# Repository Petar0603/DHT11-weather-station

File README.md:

# DHT11-weather-station
Weather station with DHT11 sensor, PCB is made in KiCad 9.0 and STM32 microcontroller code is for Arduino IDE.

---
## About
DHT11 sensor is temperature and humidity sensor, it's output is presented on an SSD1306 OLED display.
Power supply circuit is based on MB102 protoboard power supply, it is used for 3.3V stable output.
STM32F103C8T6 microcontroller is used, programming is done via SWD (Serial Wire Debug).

---
## PCB
For PCB, libraries for DHT11 and 32.768kHz crystal oscillator needed to be made in KiCad.
<div align="center">  </div>

---
## Prototype
<div align="center">  </div>
A more detailed look on connections on the protoboard.
<div align="center">  </div>

---

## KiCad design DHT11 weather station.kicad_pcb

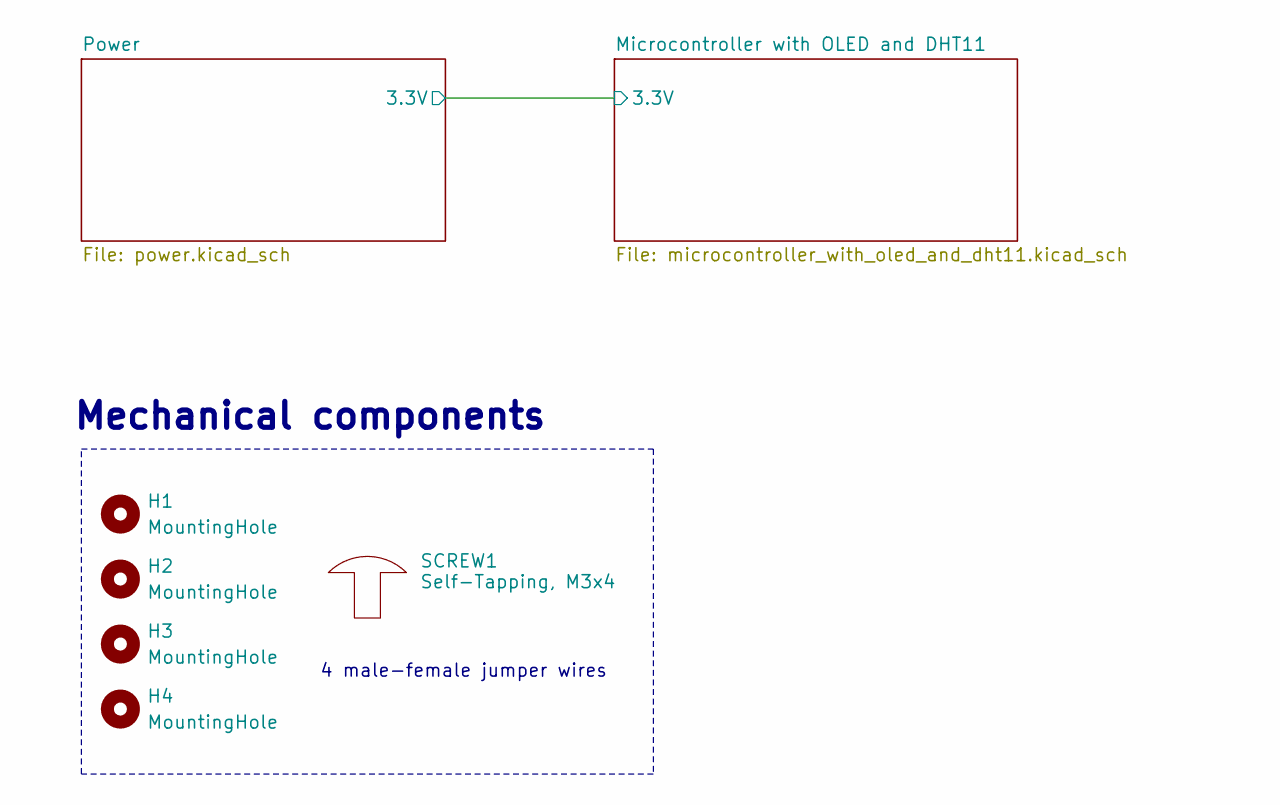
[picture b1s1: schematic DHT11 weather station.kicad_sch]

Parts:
H1, H2, H3, H4: MountingHole; MountingHole_3.2mm_M3
SCREW1: Self-Tapping, M3x4; Farnell 1420120

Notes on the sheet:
Mechanical components
4 male-female jumper wires

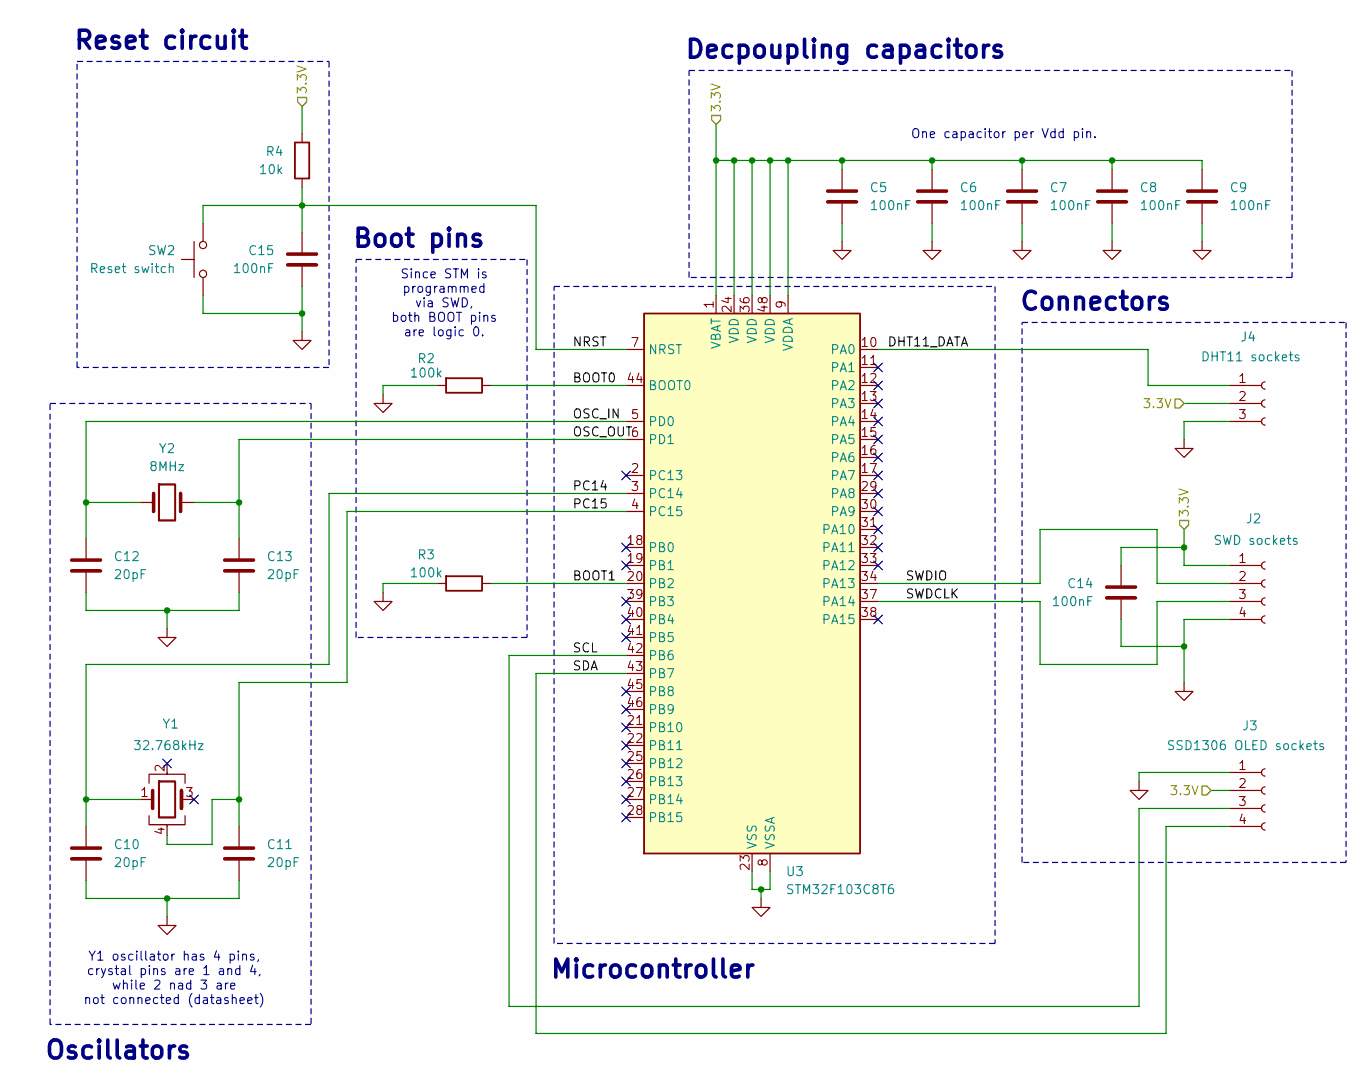
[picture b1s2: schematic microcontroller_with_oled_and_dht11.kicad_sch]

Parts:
C5, C6, C7, C8, C9, C14, C15: 100nF; C_1206_3216Metric
C10, C11, C12, C13: 20pF; C_1206_3216Metric
J2: SWD sockets; PinSocket_1x04_P2.54mm_Horizontal
J3: SSD1306 OLED sockets; PinSocket_1x04_P2.54mm_Horizontal
J4: DHT11 sockets; DHT11
R2, R3: 100k; R_1206_3216Metric
R4: 10k; R_1206_3216Metric
SW2: Reset switch; SW_Tactile_SPST_Angled_PTS645Vx83-2LFS
U3: STM32F103C8T6; LQFP-48_7x7mm_P0.5mm
Y1: 32.768kHz; XTAL_MC-306_32.7680K-G0_ROHS
Y2: 8MHz; Crystal_SMD_HC49-SD

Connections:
/Microcontroller with OLED and DHT11/3.3V: C5.1, C6.1, C7.1, C8.1, C9.1, C14.1, J2.1, J3.2, J4.2, R4.1, U3.1 (VBAT), U3.9 (VDDA), U3.24 (VDD), U3.36 (VDD), U3.48 (VDD); also elsewhere on the board
/Microcontroller with OLED and DHT11/BOOT0: R2.1, U3.44 (BOOT0)
/Microcontroller with OLED and DHT11/BOOT1: R3.1, U3.20 (PB2)
/Microcontroller with OLED and DHT11/DHT11_DATA: J4.1, U3.10 (PA0)
/Microcontroller with OLED and DHT11/NRST: C15.1, R4.2, SW2.1, U3.7 (NRST)
/Microcontroller with OLED and DHT11/OSC_IN: C12.1, U3.5 (PD0), Y2.1
/Microcontroller with OLED and DHT11/OSC_OUT: C13.1, U3.6 (PD1), Y2.2
/Microcontroller with OLED and DHT11/PC14: C10.1, U3.3 (PC14), Y1.1
/Microcontroller with OLED and DHT11/PC15: C11.1, U3.4 (PC15), Y1.4
/Microcontroller with OLED and DHT11/SCL: J3.3, U3.42 (PB6)
/Microcontroller with OLED and DHT11/SDA: J3.4, U3.43 (PB7)
/Microcontroller with OLED and DHT11/SWDCLK: J2.3, U3.37 (PA14)
/Microcontroller with OLED and DHT11/SWDIO: J2.2, U3.34 (PA13)
GND: C5.2, C6.2, C7.2, C8.2, C9.2, C10.2, C11.2, C12.2, C13.2, C14.2, C15.2, J2.4, J3.1, J4.3, R2.2, R3.2, SW2.2, U3.8 (VSSA), U3.23 (VSS), U3.35 (VSS), U3.47 (VSS); also elsewhere on the board

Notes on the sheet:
One capacitor per Vdd pin.
Y1 oscillator has 4 pins, crystal pins are 1 and 4, while 2 nad 3 are not connected (datasheet)
Oscillators
Boot pins
Reset circuit
Microcontroller
Connectors
Decpoupling capacitors
Since STM is programmed via SWD, both BOOT pins are logic 0.

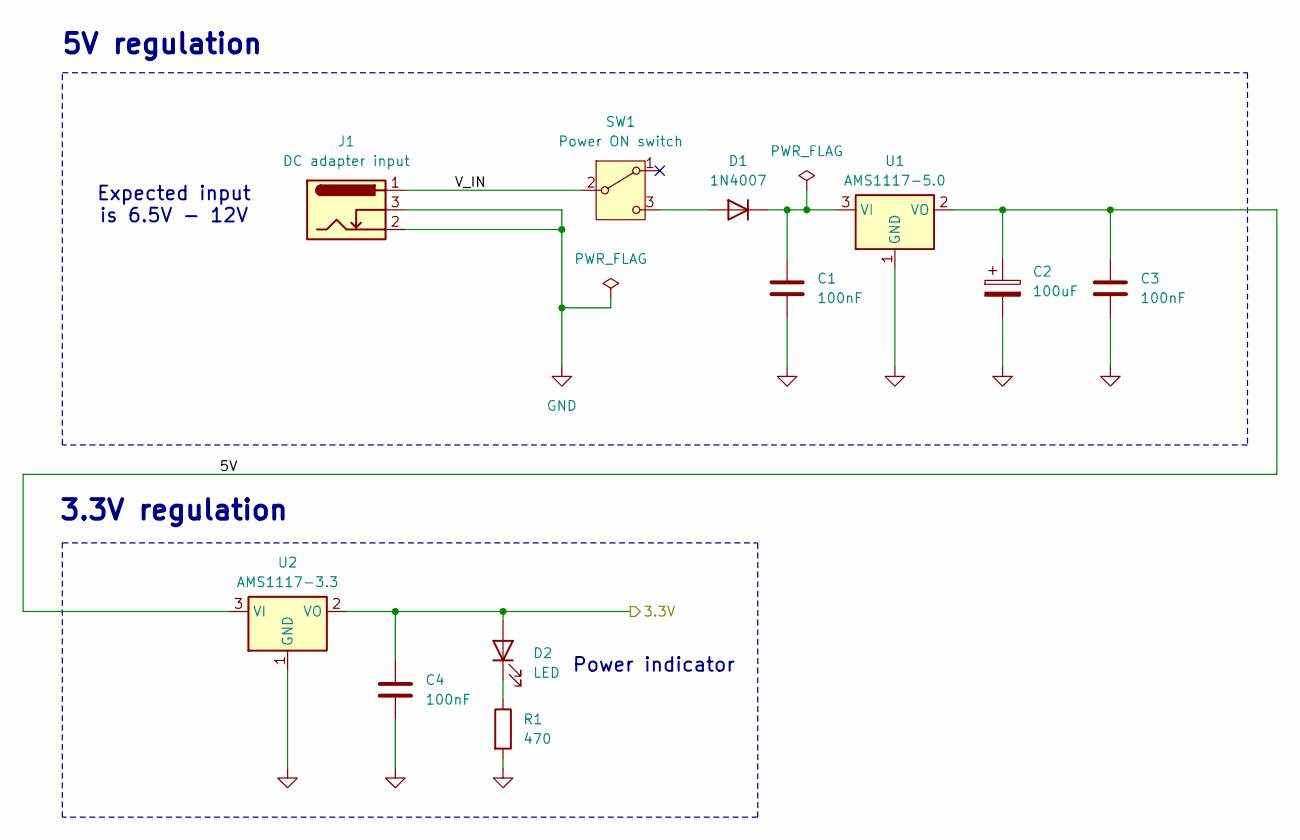
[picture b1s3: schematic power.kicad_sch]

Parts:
C1, C3, C4: 100nF; C_1206_3216Metric
C2: 100uF; CP_Radial_D4.0mm_P2.00mm
D1: 1N4007; D_SMA
D2: LED; LED_D5.0mm_Horizontal_O6.35mm_Z3.0mm
J1: DC adapter input; BarrelJack_GCT_DCJ200-10-A_Horizontal
R1: 470; R_1206_3216Metric
SW1: Power ON switch; SW_E-Switch_EG1224_SPDT_Angled
U1: AMS1117-5.0; SOT-223-3_TabPin2
U2: AMS1117-3.3; SOT-223-3_TabPin2

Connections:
/Microcontroller with OLED and DHT11/3.3V: C4.1, D2.2 (A), U2.2 (VO); also elsewhere on the board
/Power/5V: C2.1, C3.1, U1.2 (VO), U2.3 (VI)
/Power/V_IN: J1.1, SW1.2 (B)
GND: C1.2, C2.2, C3.2, C4.2, J1.2, J1.3, R1.2, U1.1 (GND), U2.1 (GND); also elsewhere on the board
unnamed: D1.2 (A), SW1.3 (C)
unnamed: C1.1, D1.1 (K), U1.3 (VI)
unnamed: D2.1 (K), R1.1

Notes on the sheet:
5V regulation
Power indicator
3.3V regulation
Expected input is 6.5V - 12V

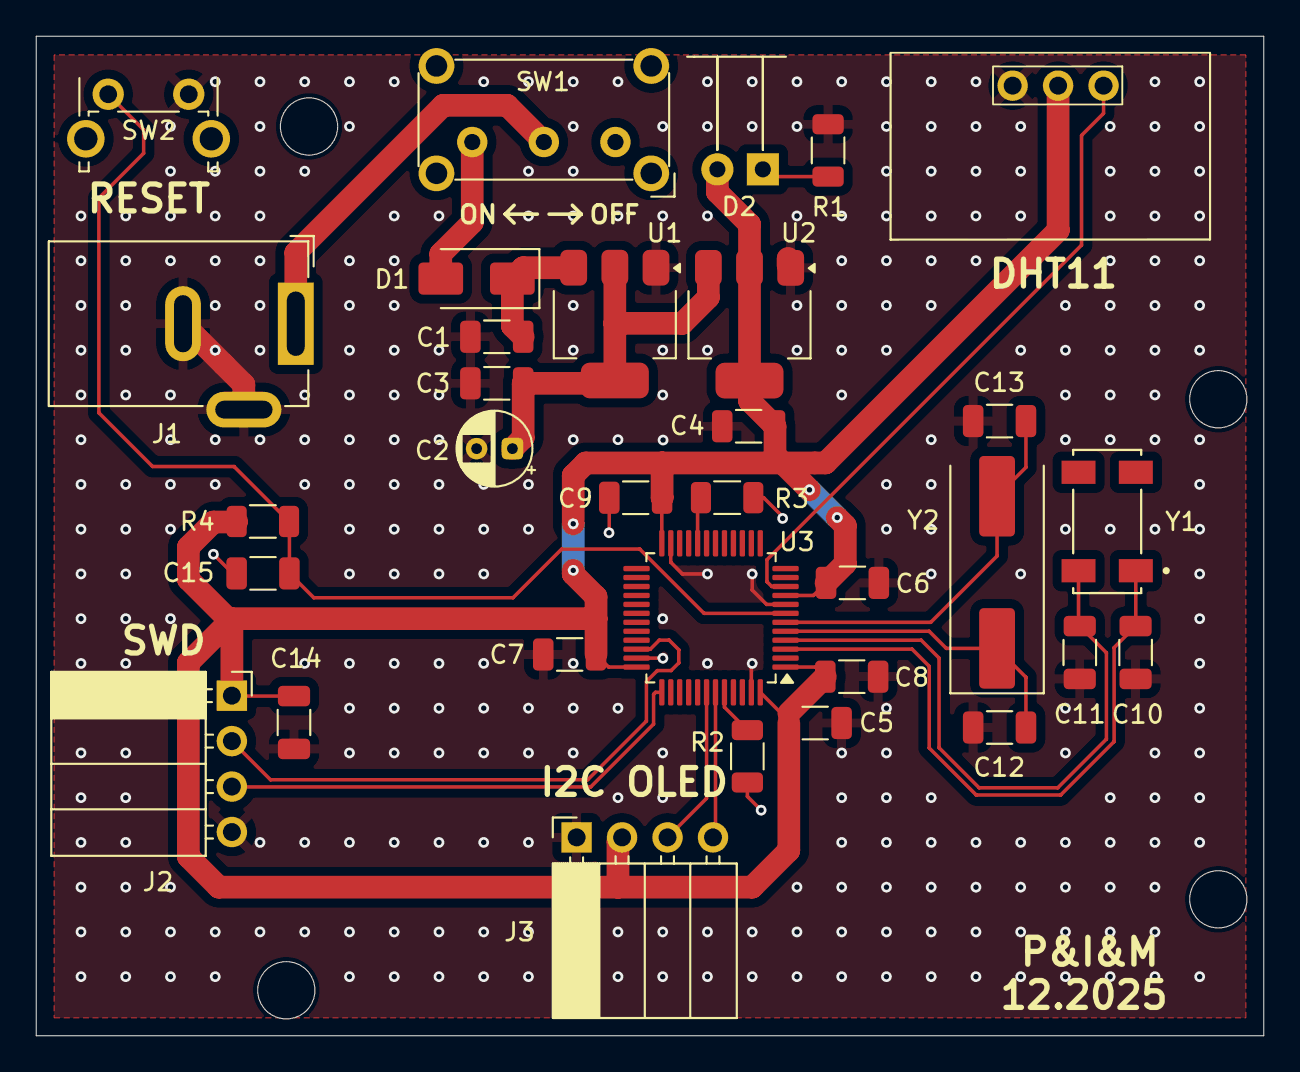
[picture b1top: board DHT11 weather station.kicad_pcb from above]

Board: 2 copper layers, 68.6 x 55.8 mm, 36 parts (0 on the bottom side), 19 nets.

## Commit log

2026-01-15 Optimized code commit
2026-01-15 Removed screw symbol from schematic and added it to BOM along with jumper wires commit
2026-01-15 Added the new scheamtic file
2026-01-15 Removed unneccessary log file commit
2026-01-15 Added the step model for housing commit
